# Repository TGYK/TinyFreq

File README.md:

# TinyFreq
An ATTiny85-based frequency multiplier for use in 1984-1985 Pontiac Fieros for digital cruise control conversion. May be applicable in other use cases. The PCB is designed to be plugged into the harness at C246 where the old cruise control servo control module plugged in, and jumpers relevant stalk signals to back of vehicle via old servo control wires. See table below for details.
|Function|Vacuum Cruise Connector|
|-:|:-|
|Set/Coast|A|
|Multiplied VSS|B|
|GND|C|
|Resume/Acc|D|
|Cruise Enable|E|

## Bill of Materials

|Reference|Device|Value|
|--------:|:----:|:----|
|R1|Resistor|100Ω|
|R2|Resistor|10kΩ|
|R3|Resistor|10kΩ|
|R4|Resistor|10kΩ|
|C1|Capacitor|N/A|
|C2|Capacitor|0.33㎌|
|C3|Capacitor|0.1u㎌|
|D1|Diode|1N4001|
|D2|TVS Diode|SA16A|
|D3|TVS Diode|SA30A|
|D4|TVS Diode|SA30A|
|Q1|N-Channel Enhancement FET|2N7000|
|Q2|N-Channel Enhancement FET|2N7000|
|U1|Linear Voltage Regulator|L78L05|
|U2|Microcontroller|ATTiny85|
|J2|Pin Header|2x3, 2.54mm|

## Uploading
### Using an Arduino Uno/Mega as a a programmer.
**THESE STEPS ARE CURRENTLY UNTESTED - FOLLOW AT YOUR OWN RISK**
1. [Setup your Arduino as a programmer and wire to the ISP connection](https://docs.arduino.cc/built-in-examples/arduino-isp/ArduinoISP/), but do not attempt to burn a bootloader to the target.
2. Open the PlatformIO project in VSCode and verify the project builds by clicking the checkmark on the toolbar at the bottom left of the window.
3. Modify the line ```upload_port = SERIAL_PORT_HERE``` within platformio.ini to reflect the serial port that your arduino-as-programmer is connected to, and save the file.
4. If using an arduino mega, modify the line ```${platformio.packages_dir}/tool-avrdude/avrdude.conf``` within platformio.ini to be ```${platformio.packages_dir}/tool-avrdude-megaavr/avrdude.conf``` and save the file.
4. Select the "program_via_ArduinoISP" environment on the bottom toolbar
5. Click the "Upload" arrow on the bottom toolbar

# THIS PROJECT WAS PROUDLY MADE WITHOUT THE USE OF "AI" OR LLM CHATBOTS.

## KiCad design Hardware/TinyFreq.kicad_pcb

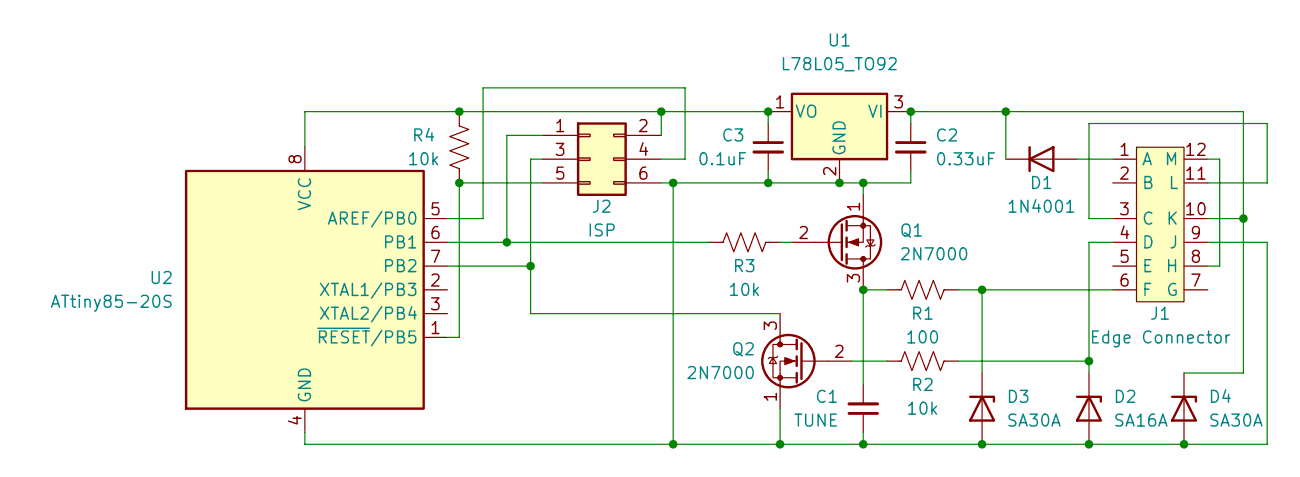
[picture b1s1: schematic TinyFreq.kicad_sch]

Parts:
C1: TUNE; C_Axial_L3.8mm_D2.6mm_P7.50mm_Horizontal
C2: 0.33uF; C_Axial_L3.8mm_D2.6mm_P7.50mm_Horizontal
C3: 0.1uF; C_Axial_L3.8mm_D2.6mm_P7.50mm_Horizontal
D1: 1N4001; D_DO-41_SOD81_P10.16mm_Horizontal
D2: SA16A; D_A-405_P7.62mm_Horizontal
D3, D4: SA30A; D_A-405_P7.62mm_Horizontal
J1: Edge Connector; CRUISE_EDGE
J2: ISP; PinHeader_2x03_P2.54mm_Vertical
Q1, Q2: 2N7000; TO-92_Inline
R1: 100; R_Axial_DIN0204_L3.6mm_D1.6mm_P5.08mm_Horizontal
R2, R3, R4: 10k; R_Axial_DIN0204_L3.6mm_D1.6mm_P5.08mm_Horizontal
U1: L78L05_TO92; TO-92_Inline
U2: ATtiny85-20S; DIP-8_W7.62mm

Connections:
unnamed: C1.1, C2.2, C3.2, D2.2 (A), D3.2 (A), D4.2 (A), J1.9 (J), J2.6, Q1.1 (S), Q2.1 (S), U1.2 (GND), U2.4 (GND)
unnamed: C1.2, Q1.3 (D), R1.1
unnamed: C2.1, D1.1 (K), D4.1 (K), J1.10 (K), U1.3 (VI)
unnamed: C3.1, J2.2, R4.2, U1.1 (VO), U2.8 (VCC)
unnamed: D1.2 (A), J1.1 (A)
unnamed: D2.1 (K), J1.4 (D), R2.2
unnamed: D3.1 (K), J1.6 (F), R1.2
unnamed: J1.3 (C), J1.11 (L)
unnamed: J1.8 (H), J1.12 (M)
unnamed: J2.1, R3.2, U2.6 (PB1)
unnamed: J2.3, Q2.3 (D), U2.7 (PB2)
unnamed: J2.4, U2.5 (AREF/PB0)
unnamed: J2.5, R4.1, U2.1 (~RESET/PB5)
unnamed: Q1.2 (G), R3.1
unnamed: Q2.2 (G), R2.1

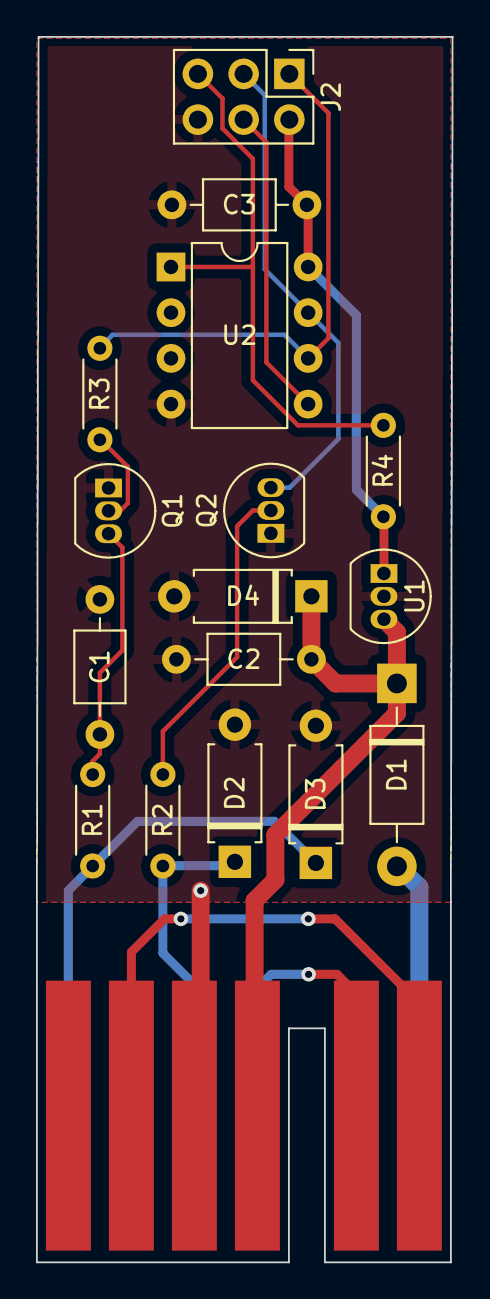
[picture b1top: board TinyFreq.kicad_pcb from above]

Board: 2 copper layers, 23.1 x 68.1 mm, 17 parts (0 on the bottom side), 15 nets.

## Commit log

2025-08-31 Initial commit - Schematics, PCB, Code
2025-09-01 Interrupt cleanup and operation prioritization, clearer commentson logic.
2025-09-01 Update schematic datasheets and symbols for TVS diodes, update PCB footprints to reflect the pin change.
2025-09-01 Generated gerberfiles, updated readme.
2025-09-01 Fix readme formatting
2025-09-02 Updated Schematic/PCB Reference values, update readme, zip gerbers.
2025-09-02 Update gerbers to reflect previous reference changes
